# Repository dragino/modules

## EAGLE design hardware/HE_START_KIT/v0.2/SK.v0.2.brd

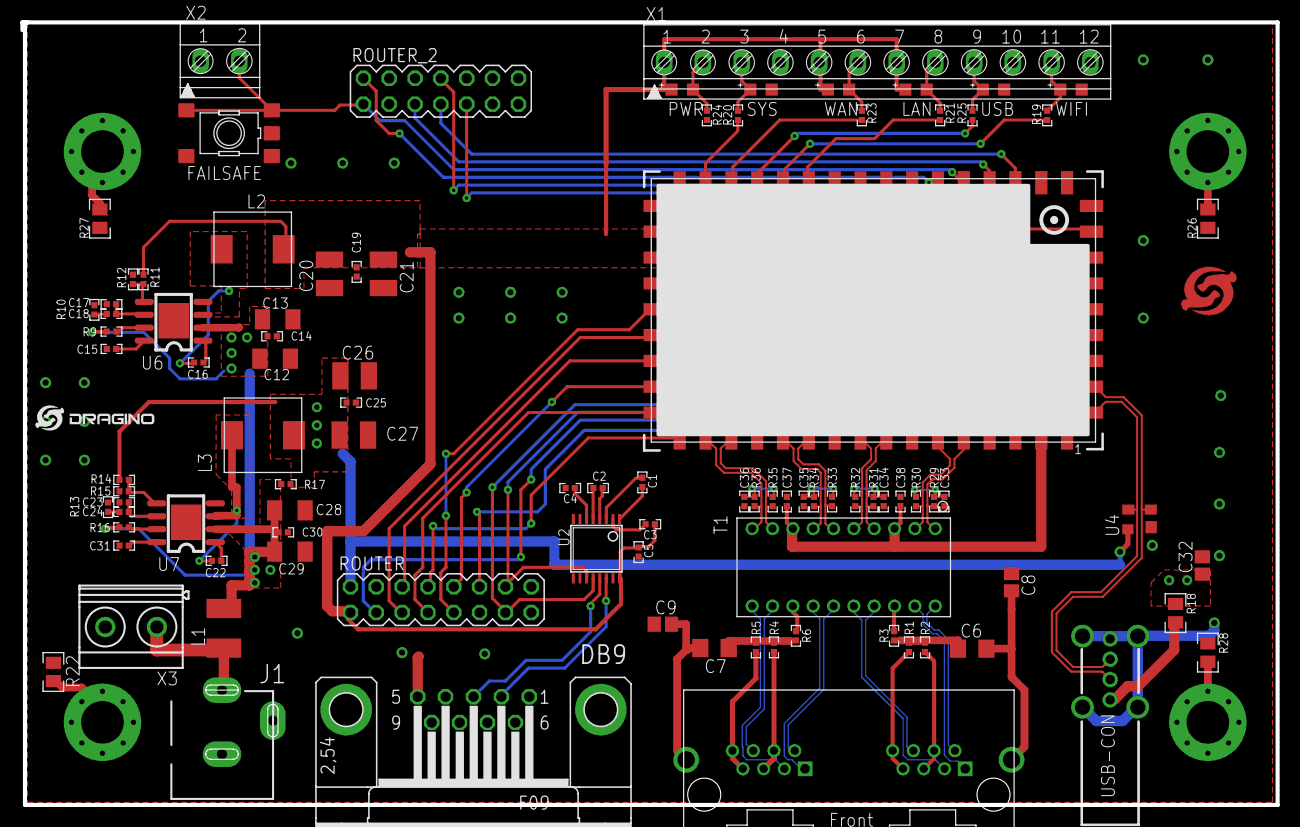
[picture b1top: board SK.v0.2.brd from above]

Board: 2 copper layers, 123.4 x 77.0 mm, 101 parts (0 on the bottom side), 92 nets.

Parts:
C1, C2, C3, C4, C5, C37, C38: 0.1u; C0402
C6, C7: 1000pF,2kv; C1206
C8, C9: 0.1u,100V; C0805
C12, C28: 10uf,25v; C1206K
C13, C29: 10u,25v; C1206K
C14, C17, C19, C23, C25, C30: NL; C0402
C15, C31: 0.1u,10v; C0402
C16, C22: 0.01u,16v; C0402
C18, C24: 3900pf,25v; C0402
C20, C21, C26, C27: 22u,10v; C1210
C32: 10u,10V; C0805
C33, C34, C35, C36: 0.1u 10v; C0402
DB9: F09HP
FAILSAFE: TS42
J1: POWER_JACKSLT; POWER_JACK_SLOT
J2: ETHERNET_2PORT; ETHERNET-1X2
L1: 2A; L1812
L2: 10uH; INDUCTOR-74
L3: 15uH; INDUCTOR-74
LAN: CHIP-LED0805
PWR: CHIP-LED0805
R1, R2, R3, R4, R5, R6: 75; R0402
R9, R16: 100K; R0402
R10, R13: 6.81K; R0402
R11: 26.1K; R0402
R12, R15: 10K; R0402
R14: 45.3K; R0402
R17: NL; R0402
R18: 0R; R0805
R19, R20, R25: 270; R0402
R21, R23, R24: 330; R0402
R22, R26, R27, R28: NL; R0805
R29, R30, R31, R32, R33, R34, R35, R36: 49.9; R0402
ROUTER: MA08-2
ROUTER_2: MA07-2
SYS: CHIP-LED0805
T1: RJ45_TRANSFORMER_HST2038DR; RIONET_H2038
U1: HE; HE50
U2: ADM3202A"; MAXIM_-_??_TSSOP16
U4: YSSR05; SOT143
U6, U7: RT8250; RT8250-SOP8
U$1: LOGO-NEW; LOGO-SILK-NEW
U$2: DRGAINO_LOGO_STOP
U$11, U$12, U$13, U$14: METAL-HOLE; METAL_HOLE
USB: CHIP-LED0805
USB-CON: USB-CON-AVERTICAL; CON-USB-AH
WAN: CHIP-LED0805
WIFI: CHIP-LED0805
X1: 12POL381
X2: 2POL381
X3: MKDSN1,5/2-5,08

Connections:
2.0V_CTL: C37.1, C38.1, T1.3, T1.8, U1.2
3.3V: C3.1, C5.2, C19.2, C20.1, C21.1, L2.P$2, LAN.A, PWR.A, R11.2, ROUTER.1, U1.23, U1.24, U2.16, WAN.A, X1.1, X1.5, X1.7
+5V: C25.2, C26.1, C27.1, C32.1, L3.P$2, R14.2, R17.1, R18.1, ROUTER.2, U4.4
AGND: C6.2, C7.2, C8.2, C9.2, J2.S1, J2.S2
GND: C4.2, C5.1, C8.1, C9.1, C12.2, C13.2, C14.2, C15.2, C17.1, C19.1, C20.2, C21.2, C23.1, C25.1, C26.2, C27.2, C28.2, C29.2, C30.2, C31.2, C32.2, C33.2, C34.2, C35.2, C36.2, C37.2, C38.2, DB9.5, FAILSAFE.1, FAILSAFE.2, J1.GND@1, J1.GND@2, R10.1, R12.1, R13.1, R15.1, R22.1, R24.1, R26.1, R27.1, R28.1, ROUTER.4, ROUTER.11, ROUTER_2.3, ROUTER_2.14, SYS.C, U1.1, U1.4, U1.7, U1.10, U1.13, U1.22, U1.25, U1.26, U1.32, U1.35, U1.40, U1.42, U1.44, U1.45, U1.48, U2.15, U4.1, U6.4, U6.9, U7.4, U7.9, USB.C, USB-CON.4, USB-CON.5, USB-CON.6, USB-CON.7, USB-CON.8, WIFI.C, X1.4, X1.10, X1.12, X2.1, X3.2
GPIO11: FAILSAFE.3, FAILSAFE.4, ROUTER_2.1, U1.37, X2.2
GPIO12: ROUTER_2.2, U1.36
GPIO15: ROUTER_2.5, U1.38
GPIO16: ROUTER_2.7, U1.39
GPIO18: ROUTER.10, U1.18
GPIO19: ROUTER.6, U1.19
GPIO20: ROUTER.5, U1.20
GPIO21: ROUTER.8, U1.16
GPIO22: ROUTER.7, U1.17
GPIO23: ROUTER.9, U1.21
GPIO24: ROUTER.12, U1.3
GPIO26: ROUTER_2.9, U1.47
GPIO27: ROUTER_2.8, U1.46
GPIO28: R20.1, U1.27
LED0: R19.1, U1.30
LED1: R25.1, U1.29
LED2: R21.1, U1.31
LED6: R23.1, U1.28
unnamed: C1.2, U2.3
unnamed: C1.1, U2.1
unnamed: C2.2, U2.4
unnamed: C2.1, U2.5
unnamed: C3.2, U2.2
unnamed: C4.1, U2.6
unnamed: R6.1, T1.13
unnamed: DB9.2, U2.14
unnamed: DB9.3, U2.13
unnamed: J1.PWR, L1.1, X3.1
unnamed: R9.1, U6.7
unnamed: R22.2, U$11.P$1
unnamed: C15.1, U6.8
unnamed: C16.1, U6.1
unnamed: C16.2, L2.P$1, U6.3
unnamed: C17.2, C18.2, U6.6
unnamed: C18.1, R10.2
unnamed: R18.2, USB-CON.1
unnamed: R11.1, R12.2, U6.5
unnamed: R19.2, WIFI.A, X1.11
unnamed: C22.1, U7.1
unnamed: C22.2, L3.P$1, U7.3
unnamed: C23.2, C24.2, U7.6
unnamed: C24.1, R13.2
unnamed: R20.2, SYS.A, X1.3
unnamed: R14.1, R15.2, U7.5
unnamed: LAN.C, R21.2, X1.8
unnamed: R16.1, U7.7
unnamed: C31.1, U7.8
unnamed: R26.2, U$12.P$1
unnamed: R23.2, WAN.C, X1.6
unnamed: PWR.C, R24.2, X1.2
unnamed: R25.2, USB.A, X1.9
unnamed: R27.2, U$13.P$1
unnamed: R28.2, U$14.P$1
unnamed: C35.1, R33.2, R34.2
unnamed: C36.1, R35.2, R36.2
unnamed: J2.2-7, J2.2-8, R1.2
unnamed: J2.2-4, J2.2-5, R2.2
unnamed: C33.1, R29.2, R30.2
unnamed: C34.1, R31.2, R32.2
unnamed: R3.1, T1.18
unnamed: C6.1, R1.1, R2.1, R3.2
unnamed: J2.1-7, J2.1-8, R5.2
unnamed: J2.1-4, J2.1-5, R4.2
unnamed: C7.1, R4.1, R5.1, R6.2
NC: ROUTER.15, ROUTER.16
P0_RX_N: R31.1, T1.4, U1.8
P0_RX_P: R32.1, T1.5, U1.9
P0_R_N: J2.2-6, T1.17
P0_R_P: J2.2-3, T1.16
P0_TX_N: R29.1, T1.1, U1.5
P0_TX_P: R30.1, T1.2, U1.6
P0_T_N: J2.2-2, T1.20
P0_T_P: J2.2-1, T1.19
P4_RX_N: R35.1, T1.9, U1.14
P4_RX_P: R36.1, T1.10, U1.15
P4_R_N: J2.1-6, T1.12
P4_R_P: J2.1-3, T1.11
P4_TX_N: R33.1, T1.6, U1.11
P4_TX_P: R34.1, T1.7, U1.12
P4_T_N: J2.1-2, T1.15
P4_T_P: J2.1-1, T1.14
RESET_ROUTE: ROUTER.3, U1.43
UART_RX: ROUTER.13, U1.33, U2.12
UART_TX: ROUTER.14, U1.34, U2.11
USB_N: U1.50, U4.3, USB-CON.2
USB_P: U1.49, U4.2, USB-CON.3
VIN: C12.1, C13.1, C14.1, C28.1, C29.1, C30.1, L1.2, R9.2, R16.2, R17.2, U6.2, U7.2

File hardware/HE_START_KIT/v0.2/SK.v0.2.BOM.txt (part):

Partlist

Exported from SK.v0.2.sch at 2014/7/24 9:05:19

EAGLE Version 6.1.0 Copyright (c) 1988-2012 CadSoft

Assembly variant: 

Part     Value                      Device                     Package            Library         Sheet

C1       0.1u                       C-EUC0402                  C0402              dragino         3
C2       0.1u                       C-EUC0402                  C0402              dragino         3
C3       0.1u                       C-EUC0402                  C0402              dragino         3
C4       0.1u                       C-EUC0402                  C0402              dragino         3
C5       0.1u                       C-EUC0402                  C0402              dragino         3
C6       1000pF,2kv                 C-EUC1206                  C1206              dragino         3
C7       1000pF,2kv                 C-EUC1206                  C1206              dragino         3
C8       0.1u,100V                  C-EUC0805                  C0805              dragino         3
C9       0.1u,100V                  C-EUC0805                  C0805              dragino         3
C12      10uf,25v                   C-EUC1206K                 C1206K             dragino         2
C13      10u,25v                    C-EUC1206K                 C1206K             dragino         2
C14      NL                         C-EUC0402                  C0402              dragino         2
C15      0.1u,10v                   C-EUC0402                  C0402              dragino         2
C16      0.01u,16v                  C-EUC0402                  C0402              dragino         2
C17      NL                         C-EUC0402                  C0402              dragino         2
C18      3900pf,25v                 C-EUC0402                  C0402              dragino         2
C19      NL                         C-EUC0402                  C0402              dragino         2
C20      22u,10v                    C-EUC1210                  C1210              dragino         2
C21      22u,10v                    C-EUC1210                  C1210              dragino         2
C22      0.01u,16v                  C-EUC0402                  C0402              dragino         2
C23      NL                         C-EUC0402                  C0402              dragino         2
C24      3900pf,25v                 C-EUC0402                  C0402              dragino         2
C25      NL                         C-EUC0402                  C0402              dragino         2
C26      22u,10v                    C-EUC1210                  C1210              dragino         2
C27      22u,10v                    C-EUC1210                  C1210              dragino         2
C28      10uf,25v                   C-EUC1206K                 C1206K             dragino         2
C29      10u,25v                    C-EUC1206K                 C1206K             dragino         2
C30      NL                         C-EUC0402                  C0402              dragino         2
C31      0.1u,10v                   C-EUC0402                  C0402              dragino         2
C32      10u,10V                    C-EUC0805                  C0805              dragino         3
C33      0.1u 10v                   C-EUC0402                  C0402              dragino         3
C34      0.1u 10v                   C-EUC0402                  C0402              dragino         3
C35      0.1u 10v                   C-EUC0402                  C0402              dragino         3
C36      0.1u 10v                   C-EUC0402                  C0402              dragino         3
C37      0.1u                       C-EUC0402                  C0402              dragino         3
C38      0.1u                       C-EUC0402                  C0402              dragino         3
DB9                                 F09HP                      F09HP              con-subd        3
FAILSAFE                            TS42                       TS42               dragino         4
J1       POWER_JACKSLT              POWER_JACKSLT              POWER_JACK_SLOT    dragino         2
J2       ETHERNET_2PORT             ETHERNET_2PORT             ETHERNET-1X2       dragino         3
L1       2A                         L-EUL1812                  L1812              dragino         2
L2       10uH                       INDUCTOR-SMRH74            INDUCTOR-74        dragino         2
L3       15uH                       INDUCTOR-SMRH74            INDUCTOR-74        dragino         2
LAN                                 LEDCHIP-LED0805            CHIP-LED0805       dragino         4
PWR                                 LEDCHIP-LED0805            CHIP-LED0805       dragino         4
R1       75                         R-US_R0402                 R0402              dragino         3
R2       75                         R-US_R0402                 R0402              dragino         3
R3       75                         R-US_R0402                 R0402              dragino         3
R4       75                         R-US_R0402                 R0402              dragino         3
R5       75                         R-US_R0402                 R0402              dragino         3
R6       75                         R-US_R0402                 R0402              dragino         3
R9       100K                       R-US_R0402                 R0402              dragino         2
R10      6.81K                      R-US_R0402                 R0402              dragino         2
R11      26.1K                      R-US_R0402                 R0402              dragino         2
R12      10K                        R-US_R0402                 R0402              dragino         2
R13      6.81K                      R-US_R0402                 R0402              dragino         2
R14      45.3K                      R-US_R0402                 R0402              dragino         2
R15      10K                        R-US_R0402                 R0402              dragino         2
R16      100K                       R-US_R0402                 R0402              dragino         2
R17      NL                         R-US_R0402                 R0402              dragino         2
R18      0R                         R-US_R0805                 R0805              dragino         3
R19      270                        R-US_R0402                 R0402              dragino         4
R20      270                        R-US_R0402                 R0402              dragino         4
R21      330                        R-US_R0402                 R0402              dragino         4
R22      NL                         R-US_R0805                 R0805              dragino         4
R23      330                        R-US_R0402                 R0402              dragino         4
R24      330                        R-US_R0402                 R0402              dragino         4
R25      270                        R-US_R0402                 R0402              dragino         4
R26      NL                         R-US_R0805                 R0805              dragino         4
R27      NL                         R-US_R0805                 R0805              dragino         4
R28      NL                         R-US_R0805                 R0805              dragino         4
R29      49.9                       R-US_R0402                 R0402              dragino         3
R30      49.9                       R-US_R0402                 R0402              dragino         3
R31      49.9                       R-US_R0402                 R0402              dragino         3
R32      49.9                       R-US_R0402                 R0402              dragino         3
R33      49.9                       R-US_R0402                 R0402              dragino         3
R34      49.9                       R-US_R0402                 R0402              dragino         3
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
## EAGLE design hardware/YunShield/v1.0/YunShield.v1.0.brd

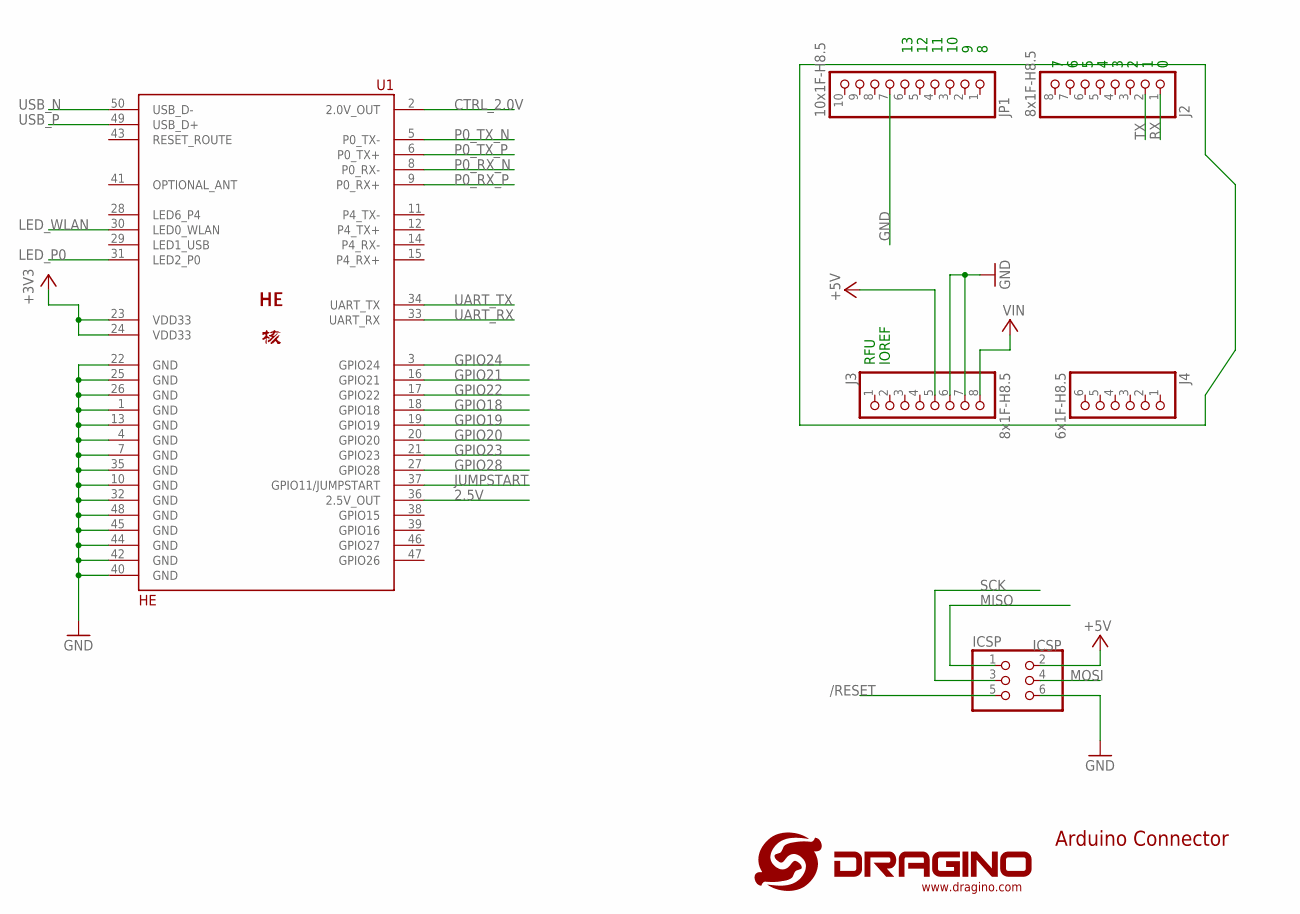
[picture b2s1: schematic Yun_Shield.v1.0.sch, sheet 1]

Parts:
ICSP: ICSP; 2X03
J2, J3: 8x1F-H8.5; 1X08
J4: 6x1F-H8.5; 1X06
JP1: 10x1F-H8.5; 1X10
U1: HE; HE50
U$1: LOGO-NEW; LOGO-SILK-NEW

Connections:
2.5V: U1.36 (2.5V_OUT); also elsewhere on the board
+3V3: U1.23 (VDD33), U1.24 (VDD33); also elsewhere on the board
+5V: ICSP.2, J3.5; also elsewhere on the board
/RESET: ICSP.5; also elsewhere on the board
CTRL_2.0V: U1.2 (2.0V_OUT); also elsewhere on the board
GND: ICSP.6, J3.6, J3.7, JP1.7, U1.1 (GND), U1.4 (GND), U1.7 (GND), U1.10 (GND), U1.13 (GND), U1.22 (GND), U1.25 (GND), U1.26 (GND), U1.32 (GND), U1.35 (GND), U1.40 (GND), U1.42 (GND), U1.44 (GND), U1.45 (GND), U1.48 (GND); also elsewhere on the board
GPIO18: U1.18 (GPIO18); also elsewhere on the board
GPIO19: U1.19 (GPIO19); also elsewhere on the board
GPIO20: U1.20 (GPIO20); also elsewhere on the board
GPIO21: U1.16 (GPIO21); also elsewhere on the board
GPIO22: U1.17 (GPIO22); also elsewhere on the board
GPIO23: U1.21 (GPIO23); also elsewhere on the board
GPIO24: U1.3 (GPIO24); also elsewhere on the board
GPIO28: U1.27 (GPIO28); also elsewhere on the board
JUMPSTART: U1.37 (GPIO11/JUMPSTART); also elsewhere on the board
LED_P0: U1.31 (LED2_P0); also elsewhere on the board
LED_WLAN: U1.30 (LED0_WLAN); also elsewhere on the board
MISO: ICSP.1; also elsewhere on the board
MOSI: ICSP.4; also elsewhere on the board
OPTIONAL_ANT: U1.41 (OPTIONAL_ANT)
P0_RX_N: U1.8 (P0_RX-); also elsewhere on the board
P0_RX_P: U1.9 (P0_RX+); also elsewhere on the board
P0_TX_N: U1.5 (P0_TX-); also elsewhere on the board
P0_TX_P: U1.6 (P0_TX+); also elsewhere on the board
RX: J2.1; also elsewhere on the board
SCK: ICSP.3; also elsewhere on the board
TX: J2.2; also elsewhere on the board
UART_RX: U1.33 (UART_RX); also elsewhere on the board
UART_TX: U1.34 (UART_TX); also elsewhere on the board
USB_N: U1.50 (USB_D-); also elsewhere on the board
USB_P: U1.49 (USB_D+); also elsewhere on the board
VIN: J3.8; also elsewhere on the board

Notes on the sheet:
IOREF
RFU
Arduino Connector

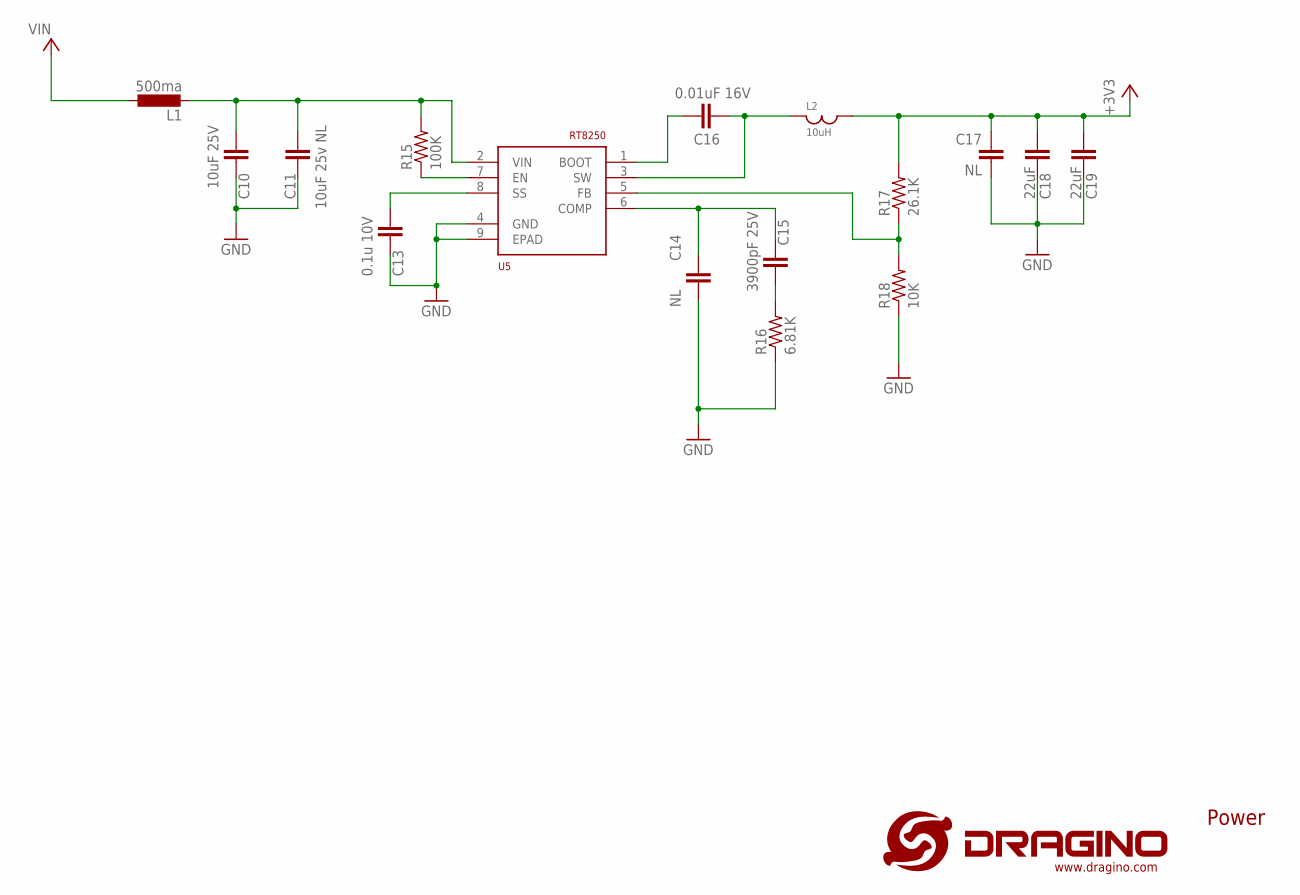
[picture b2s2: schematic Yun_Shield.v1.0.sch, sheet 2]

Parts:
C10: 10uF 25V; C1206
C11: 10uF 25v NL; C1206
C13: 0.1u 10V; C0402
C14, C17: NL; C0402
C15: 3900pF 25V; C0402
C16: 0.01uF 16V; C0402
C18, C19: 22uF; C1210
L1: 500ma; L1812
L2: 10uH; INDUCTOR-74
R15: 100K; R0402
R16: 6.81K; R0402
R17: 26.1K; R0402
R18: 10K; R0402
U5: RT8250; RT8250-SOP8

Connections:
+3V3: C17.1, C18.1, C19.1, L2.P$2, R17.2; also elsewhere on the board
GND: C10.1, C11.1, C13.2, C14.2, C17.2, C18.2, C19.2, R16.1, R18.1, U5.4 (GND), U5.9 (EPAD); also elsewhere on the board
unnamed: C10.2, C11.2, L1.2, R15.2, U5.2 (VIN)
unnamed: R15.1, U5.7 (EN)
unnamed: R17.1, R18.2, U5.5 (FB)
unnamed: C13.1, U5.8 (SS)
unnamed: C14.1, C15.1, U5.6 (COMP)
unnamed: C15.2, R16.2
unnamed: C16.1, U5.1 (BOOT)
unnamed: C16.2, L2.P$1, U5.3 (SW)
VIN: L1.1; also elsewhere on the board

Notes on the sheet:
Power

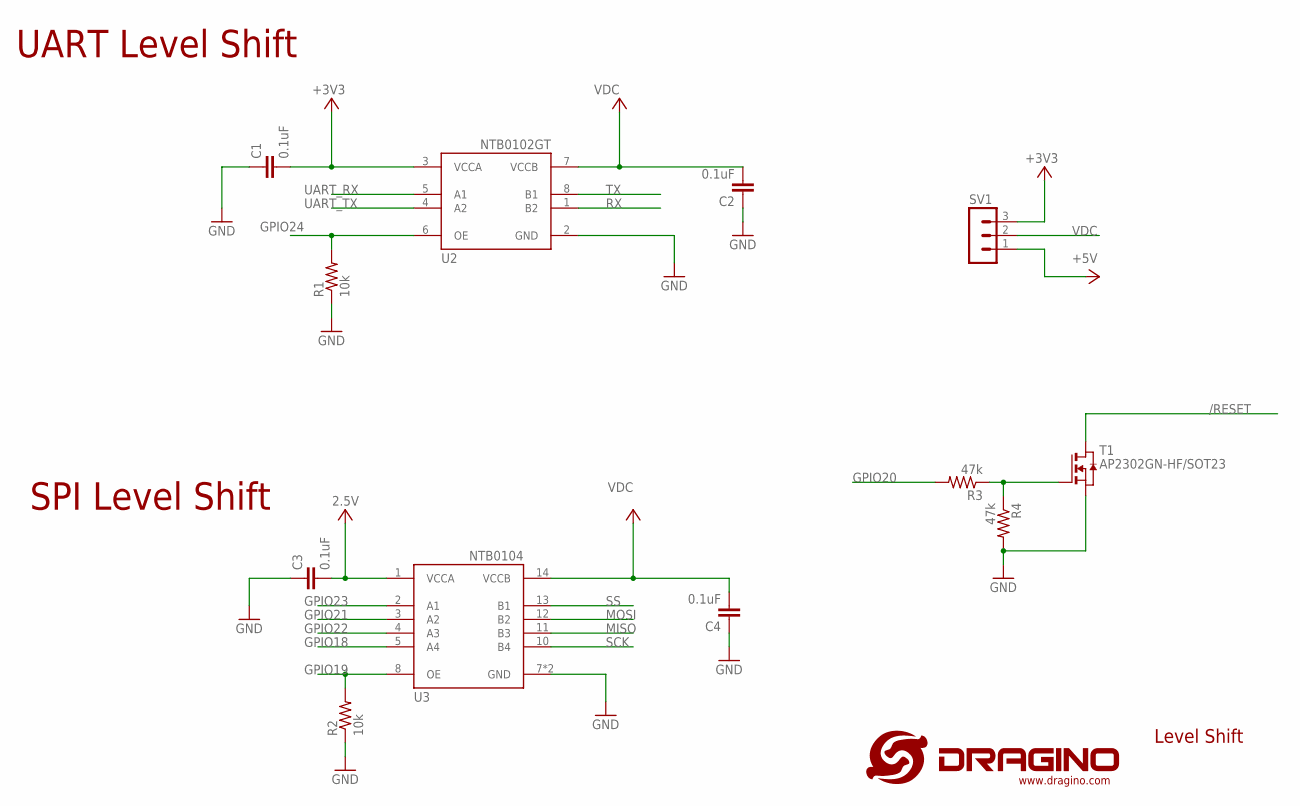
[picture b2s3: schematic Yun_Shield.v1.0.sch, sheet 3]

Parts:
C1, C2, C3, C4: 0.1uF; C0402
R1, R2: 10k; R0402
R3, R4: 47k; R0402
SV1: MA03-1
T1: AP2302GN-HF/SOT23; SOT-23
U2: NTB0102GT; NXP-SOT833-1
U3: NTB0104; DHVQFN14

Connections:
2.5V: C3.2, U3.1 (VCCA); also elsewhere on the board
+3V3: C1.2, SV1.3, U2.3 (VCCA); also elsewhere on the board
+5V: SV1.1; also elsewhere on the board
/RESET: T1.1 (D); also elsewhere on the board
GND: C1.1, C2.1, C3.1, C4.1, R1.1, R2.1, R4.2, T1.2 (S), U2.2 (GND), U3.7 (GND), U3.EXP (GND); also elsewhere on the board
GPIO18: U3.5 (A4); also elsewhere on the board
GPIO19: R2.2, U3.8 (OE); also elsewhere on the board
GPIO20: R3.2; also elsewhere on the board
GPIO21: U3.3 (A2); also elsewhere on the board
GPIO22: U3.4 (A3); also elsewhere on the board
GPIO23: U3.2 (A1); also elsewhere on the board
GPIO24: R1.2, U2.6 (OE); also elsewhere on the board
MISO: U3.11 (B3); also elsewhere on the board
MOSI: U3.12 (B2); also elsewhere on the board
unnamed: R3.1, R4.1, T1.3 (G)
RX: U2.1 (B2); also elsewhere on the board
SCK: U3.10 (B4); also elsewhere on the board
SS: U3.13 (B1)
TX: U2.8 (B1); also elsewhere on the board
UART_RX: U2.5 (A1); also elsewhere on the board
UART_TX: U2.4 (A2); also elsewhere on the board
VDC: C2.2, C4.2, SV1.2, U2.7 (VCCB), U3.14 (VCCB)

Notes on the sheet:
Level Shift
UART Level Shift
SPI Level Shift

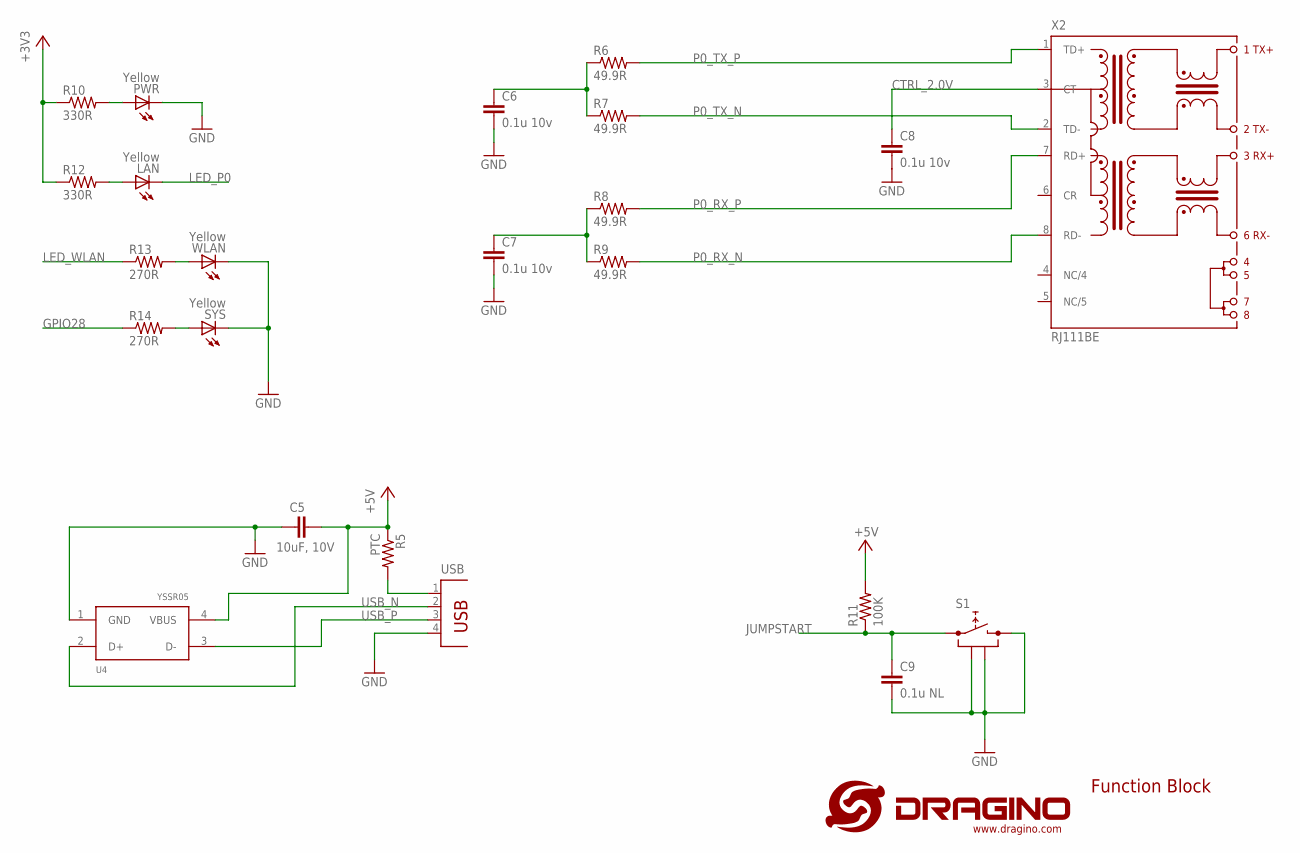
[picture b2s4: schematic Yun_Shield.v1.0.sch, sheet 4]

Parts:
C5: 10uF, 10V; C0805
C6, C7, C8: 0.1u 10v; C0402
C9: 0.1u NL; C0402
LAN: Yellow; CHIP-LED0603
PWR: Yellow; CHIP-LED0603
R5: PTC; R0805
R6, R7, R8, R9: 49.9R; R0402
R10, R12: 330R; R0402
R11: 100K; R0402
R13, R14: 270R; R0402
S1: PUSH_SWITCH; SWITCH_6X6X5
SYS: Yellow; CHIP-LED0603
U4: YSSR05; SOT143
USB: PN87520
WLAN: Yellow; CHIP-LED0603
X2: RJ111BE

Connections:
+3V3: R10.1, R12.1; also elsewhere on the board
+5V: C5.1, R5.1, R11.2, U4.4 (VBUS); also elsewhere on the board
CTRL_2.0V: C8.1, X2.3 (CT); also elsewhere on the board
GND: C5.2, C6.2, C7.2, C8.2, C9.2, PWR.C, S1.2, S1.3, S1.4, SYS.C, U4.1 (GND), USB.4, WLAN.C; also elsewhere on the board
GPIO28: R14.1; also elsewhere on the board
JUMPSTART: C9.1, R11.1, S1.1; also elsewhere on the board
LED_P0: LAN.C; also elsewhere on the board
LED_WLAN: R13.1; also elsewhere on the board
unnamed: R5.2, USB.1
unnamed: C6.1, R6.1, R7.1
unnamed: PWR.A, R10.2
unnamed: C7.1, R8.1, R9.1
unnamed: LAN.A, R12.2
unnamed: R13.2, WLAN.A
unnamed: R14.2, SYS.A
P0_RX_N: R9.2, X2.8 (RD-); also elsewhere on the board
P0_RX_P: R8.2, X2.7 (RD+); also elsewhere on the board
P0_TX_N: R7.2, X2.2 (TD-); also elsewhere on the board
P0_TX_P: R6.2, X2.1 (TD+); also elsewhere on the board
USB_N: U4.2 (D+), USB.2; also elsewhere on the board
USB_P: U4.3 (D-), USB.3; also elsewhere on the board

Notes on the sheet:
Function Block

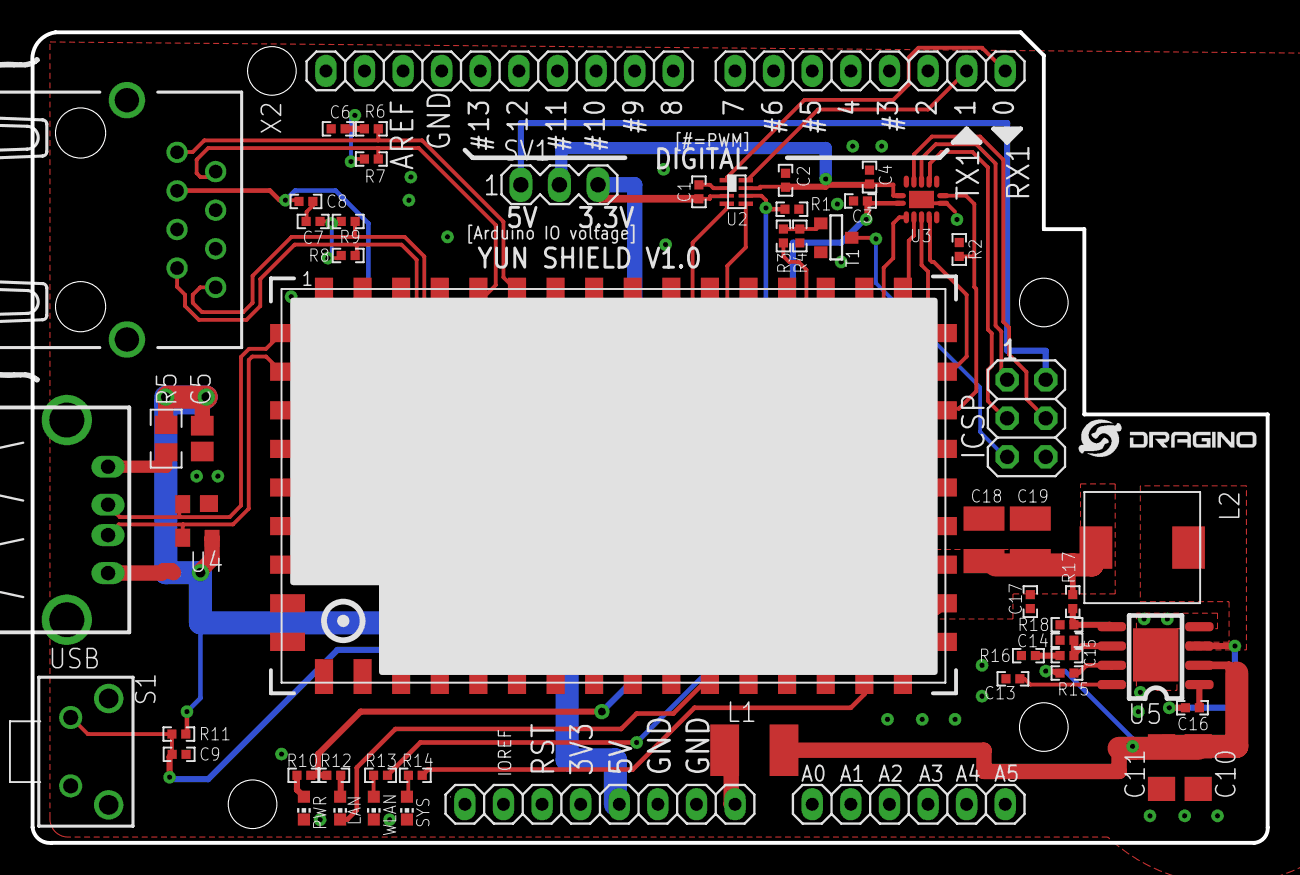
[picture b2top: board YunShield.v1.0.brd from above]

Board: 2 copper layers, 81.3 x 53.3 mm, 58 parts (0 on the bottom side), 48 nets.

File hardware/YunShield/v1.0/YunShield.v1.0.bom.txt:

Partlist

Exported from Yun_Shield.v1.0.sch at 2014/7/9 17:37:33

EAGLE Version 6.1.0 Copyright (c) 1988-2012 CadSoft

Assembly variant: 

Part     Value             Device          Package      Library  Sheet

C1       0.1uF             C-EUC0402       C0402        dragino  3
C2       0.1uF             C-EUC0402       C0402        dragino  3
C3       0.1uF             C-EUC0402       C0402        dragino  3
C4       0.1uF             C-EUC0402       C0402        dragino  3
C5       10uF, 10V         C-EUC0805       C0805        dragino  4
C6       0.1u 10v          C-EUC0402       C0402        dragino  4
C7       0.1u 10v          C-EUC0402       C0402        dragino  4
C8       0.1u 10v          C-EUC0402       C0402        dragino  4
C9       0.1u NL           C-EUC0402       C0402        dragino  4
C10      10uF 25V          C-EUC1206       C1206        dragino  2
C11      10uF 25v NL       C-EUC1206       C1206        dragino  2
C13      0.1u 10V          C-EUC0402       C0402        dragino  2
C14      NL                C-EUC0402       C0402        dragino  2
C15      3900pF 25V        C-EUC0402       C0402        dragino  2
C16      0.01uF 16V        C-EUC0402       C0402        dragino  2
C17      NL                C-EUC0402       C0402        dragino  2
C18      22uF              C-EUC1210       C1210        dragino  2
C19      22uF              C-EUC1210       C1210        dragino  2
ICSP     ICSP              PINHD-2X3       2X03         SmartPrj 1
J2       8x1F-H8.5         PINHD-1X8       1X08         SmartPrj 1
J3       8x1F-H8.5         PINHD-1X8       1X08         SmartPrj 1
J4       6x1F-H8.5         PINHD-1X6       1X06         SmartPrj 1
JP1      10x1F-H8.5        PINHD-1X10      1X10         SmartPrj 1
L1       500ma             L-EUL1812       L1812        dragino  2
L2       10uH              INDUCTOR-SMRH74 INDUCTOR-74  dragino  2
LAN      Yellow            LEDCHIP-LED0603 CHIP-LED0603 dragino  4
PWR      Yellow            LEDCHIP-LED0603 CHIP-LED0603 dragino  4
R1       10k               R-US_R0402      R0402        dragino  3
R2       10k               R-US_R0402      R0402        dragino  3
R3       47k               R-US_R0402      R0402        dragino  3
R4       47k               R-US_R0402      R0402        dragino  3
R5       PTC               R-US_R0805      R0805        dragino  4
R6       49.9R             R-US_R0402      R0402        dragino  4
R7       49.9R             R-US_R0402      R0402        dragino  4
R8       49.9R             R-US_R0402      R0402        dragino  4
R9       49.9R             R-US_R0402      R0402        dragino  4
R10      330R              R-US_R0402      R0402        dragino  4
R11      100K              R-US_R0402      R0402        dragino  4
R12      330R              R-US_R0402      R0402        dragino  4
R13      270R              R-US_R0402      R0402        dragino  4
R14      270R              R-US_R0402      R0402        dragino  4
R15      100K              R-US_R0402      R0402        dragino  2
R16      6.81K             R-US_R0402      R0402        dragino  2
R17      26.1K             R-US_R0402      R0402        dragino  2
R18      10K               R-US_R0402      R0402        dragino  2
S1                         PUSH_SWITCH     SWITCH_6X6X5 dragino  4
SV1                        MA03-1          MA03-1       con-lstb 3
SYS      Yellow            LEDCHIP-LED0603 CHIP-LED0603 dragino  4
T1       AP2302GN-HF/SOT23 NMOSFET-SOT23   SOT-23       dragino  3
U1       HE                HE              HE50         dragino  1
U2       NTB0102GT         NTB0102GT       NXP-SOT833-1 dragino  3
U3       NTB0104           NTB0104         DHVQFN14     dragino  3
U4       YSSR05            YSSR05          SOT143       dragino  4
U5       RT8250            RT8250          RT8250-SOP8  dragino  2
USB                        PN87520         PN87520      con-berg 4
WLAN     Yellow            LEDCHIP-LED0603 CHIP-LED0603 dragino  4
X2       RJ111BE           RJ111BE         RJ111BE      dragino  4

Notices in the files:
parts and their libraries:
dragino: http://creativecommons.org/licenses/by-sa/3.0
dragino: Released under the CC Attribution Share-Alike 3.0 License
